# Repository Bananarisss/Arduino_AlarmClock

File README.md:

# Arduino_AlarmClock
Code for an alarm clock made using:
<ul>
  <li>Arduino nano</li>
  <li>DFPlayerMini</li>
  <li>4x4 Membrane Keyboard</li>
  <li>16x4 LCD Display with I2C Module</li>
  <li>RTC DS3231</li>
  <li>4 Red LED Diods</li>
</ul>

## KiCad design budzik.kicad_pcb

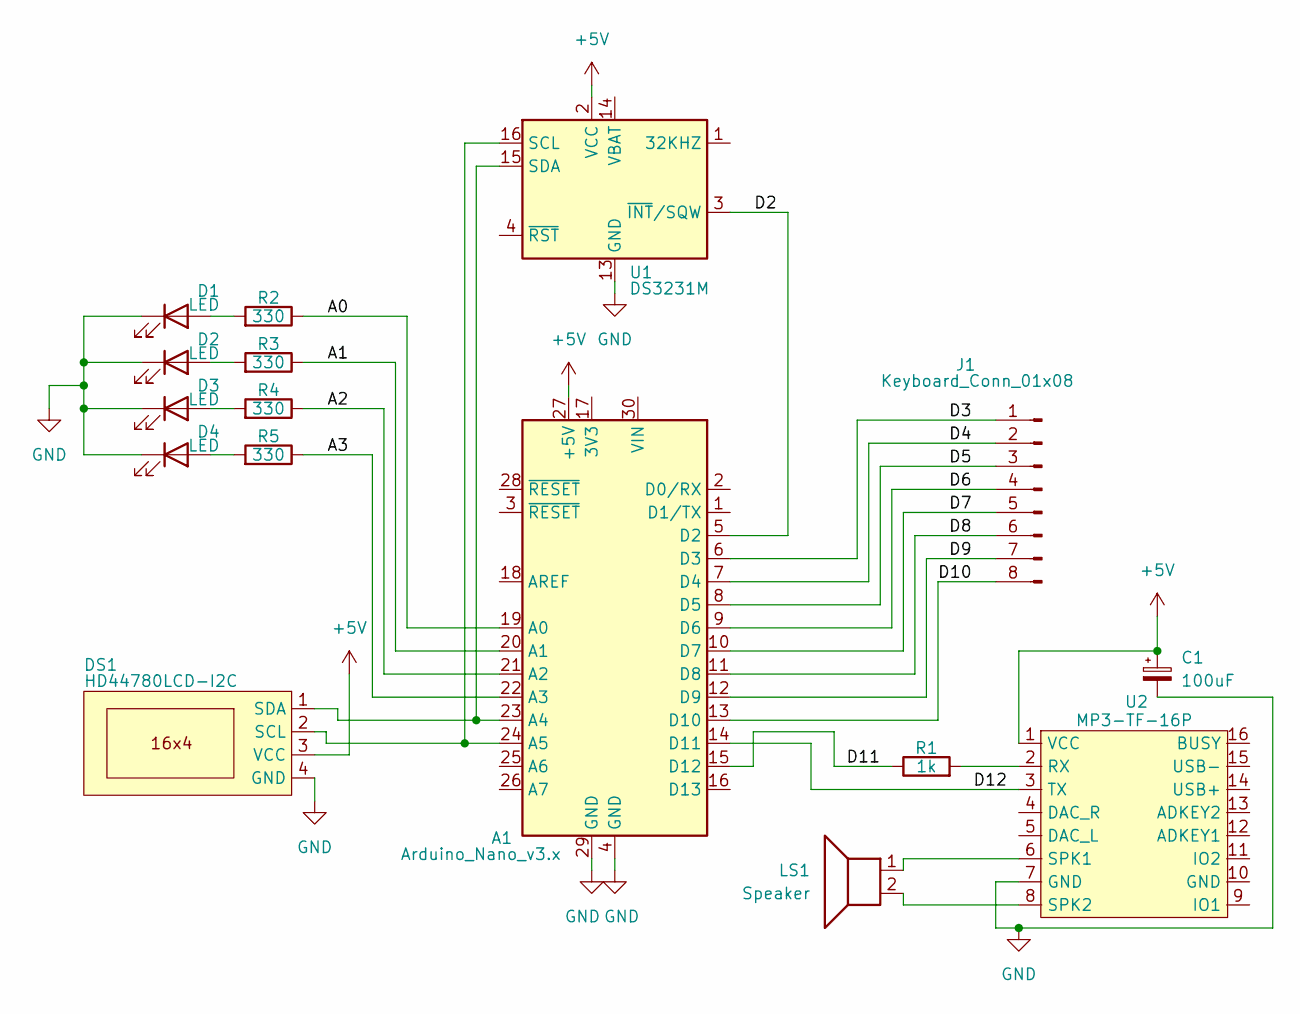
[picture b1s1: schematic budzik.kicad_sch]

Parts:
A1: Arduino_Nano_v3.x; Arduino_Nano
C1: 100uF; CP_Radial_Tantal_D4.5mm_P2.50mm
D1, D2, D3, D4: LED; LED_D5.0mm
DS1: HD44780LCD-I2C; LCD+I2C_16x4
J1: Keyboard_Conn_01x08; PinHeader_1x08_P1.00mm_Horizontal
LS1: Speaker
R1: 1k; R_Axial_DIN0207_L6.3mm_D2.5mm_P10.16mm_Horizontal
R2, R3, R4, R5: 330; R_Axial_DIN0207_L6.3mm_D2.5mm_P10.16mm_Horizontal
U1: DS3231M; DS3231
U2: MP3-TF-16P

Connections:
+5V: A1.27 (+5V), C1.1, DS1.3 (VCC), U1.2 (VCC), U2.1 (VCC)
/A0: A1.19 (A0), R2.1
/A1: A1.20 (A1), R3.1
/A2: A1.21 (A2), R4.1
/A3: A1.22 (A3), R5.1
/D2: A1.5 (D2), U1.3 (~INT/SQW)
/D3: A1.6 (D3), J1.1
/D4: A1.7 (D4), J1.2
/D5: A1.8 (D5), J1.3
/D6: A1.9 (D6), J1.4
/D7: A1.10 (D7), J1.5
/D8: A1.11 (D8), J1.6
/D9: A1.12 (D9), J1.7
/D10: A1.13 (D10), J1.8
/D11: A1.15 (D12), R1.1
/D12: A1.14 (D11), U2.3 (TX)
GND: A1.4 (GND), A1.29 (GND), C1.2, D1.1 (K), D2.1 (K), D3.1 (K), D4.1 (K), DS1.4 (GND), U1.5 (GND), U1.6 (GND), U1.7 (GND), U1.8 (GND), U1.9 (GND), U1.10 (GND), U1.11 (GND), U1.12 (GND), U1.13 (GND), U2.7 (GND)
unnamed: A1.23 (A4), DS1.1 (SDA), U1.15 (SDA)
unnamed: A1.24 (A5), DS1.2 (SCL), U1.16 (SCL)
unnamed: D1.2 (A), R2.2
unnamed: D2.2 (A), R3.2
unnamed: D3.2 (A), R4.2
unnamed: D4.2 (A), R5.2
unnamed: R1.2, U2.2 (RX)
unnamed: LS1.1, U2.6 (SPK1)
unnamed: LS1.2, U2.8 (SPK2)

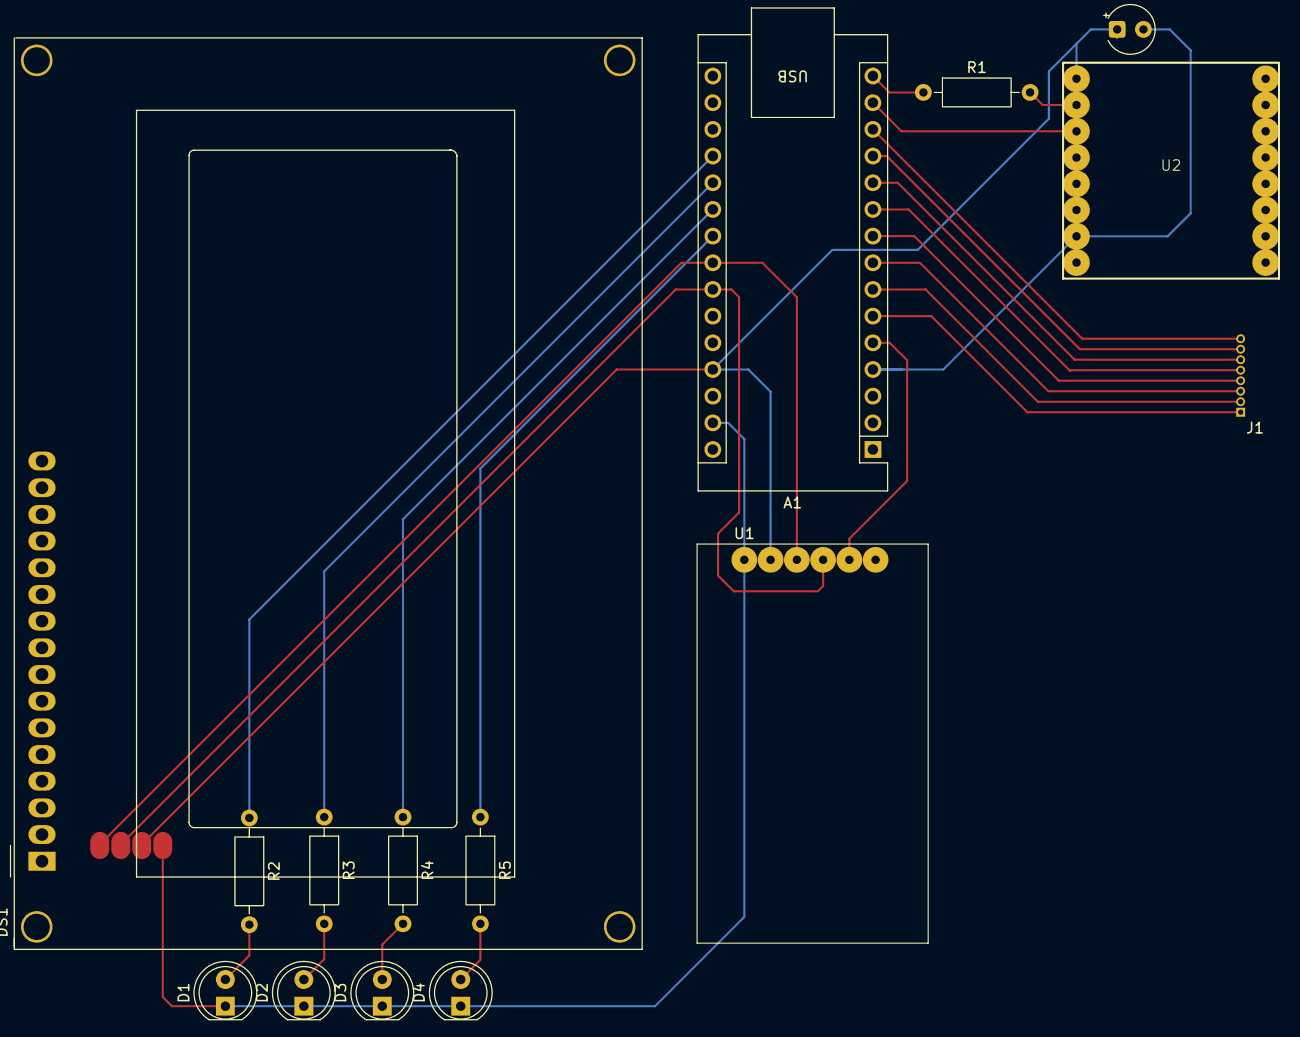
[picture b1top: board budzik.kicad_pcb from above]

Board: 2 copper layers, 15 parts (1 on the bottom side), 24 nets.

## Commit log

2025-12-31 Update README with components
2025-12-31 Working code
2025-12-31 Fixed 'C' button
2026-01-03 misc
2026-01-09 Fixed volume display and added schematic
2026-01-10 Fixed time and math task randomness
2026-01-10 added PCB schematic
2026-01-17 Clean up of global variables
